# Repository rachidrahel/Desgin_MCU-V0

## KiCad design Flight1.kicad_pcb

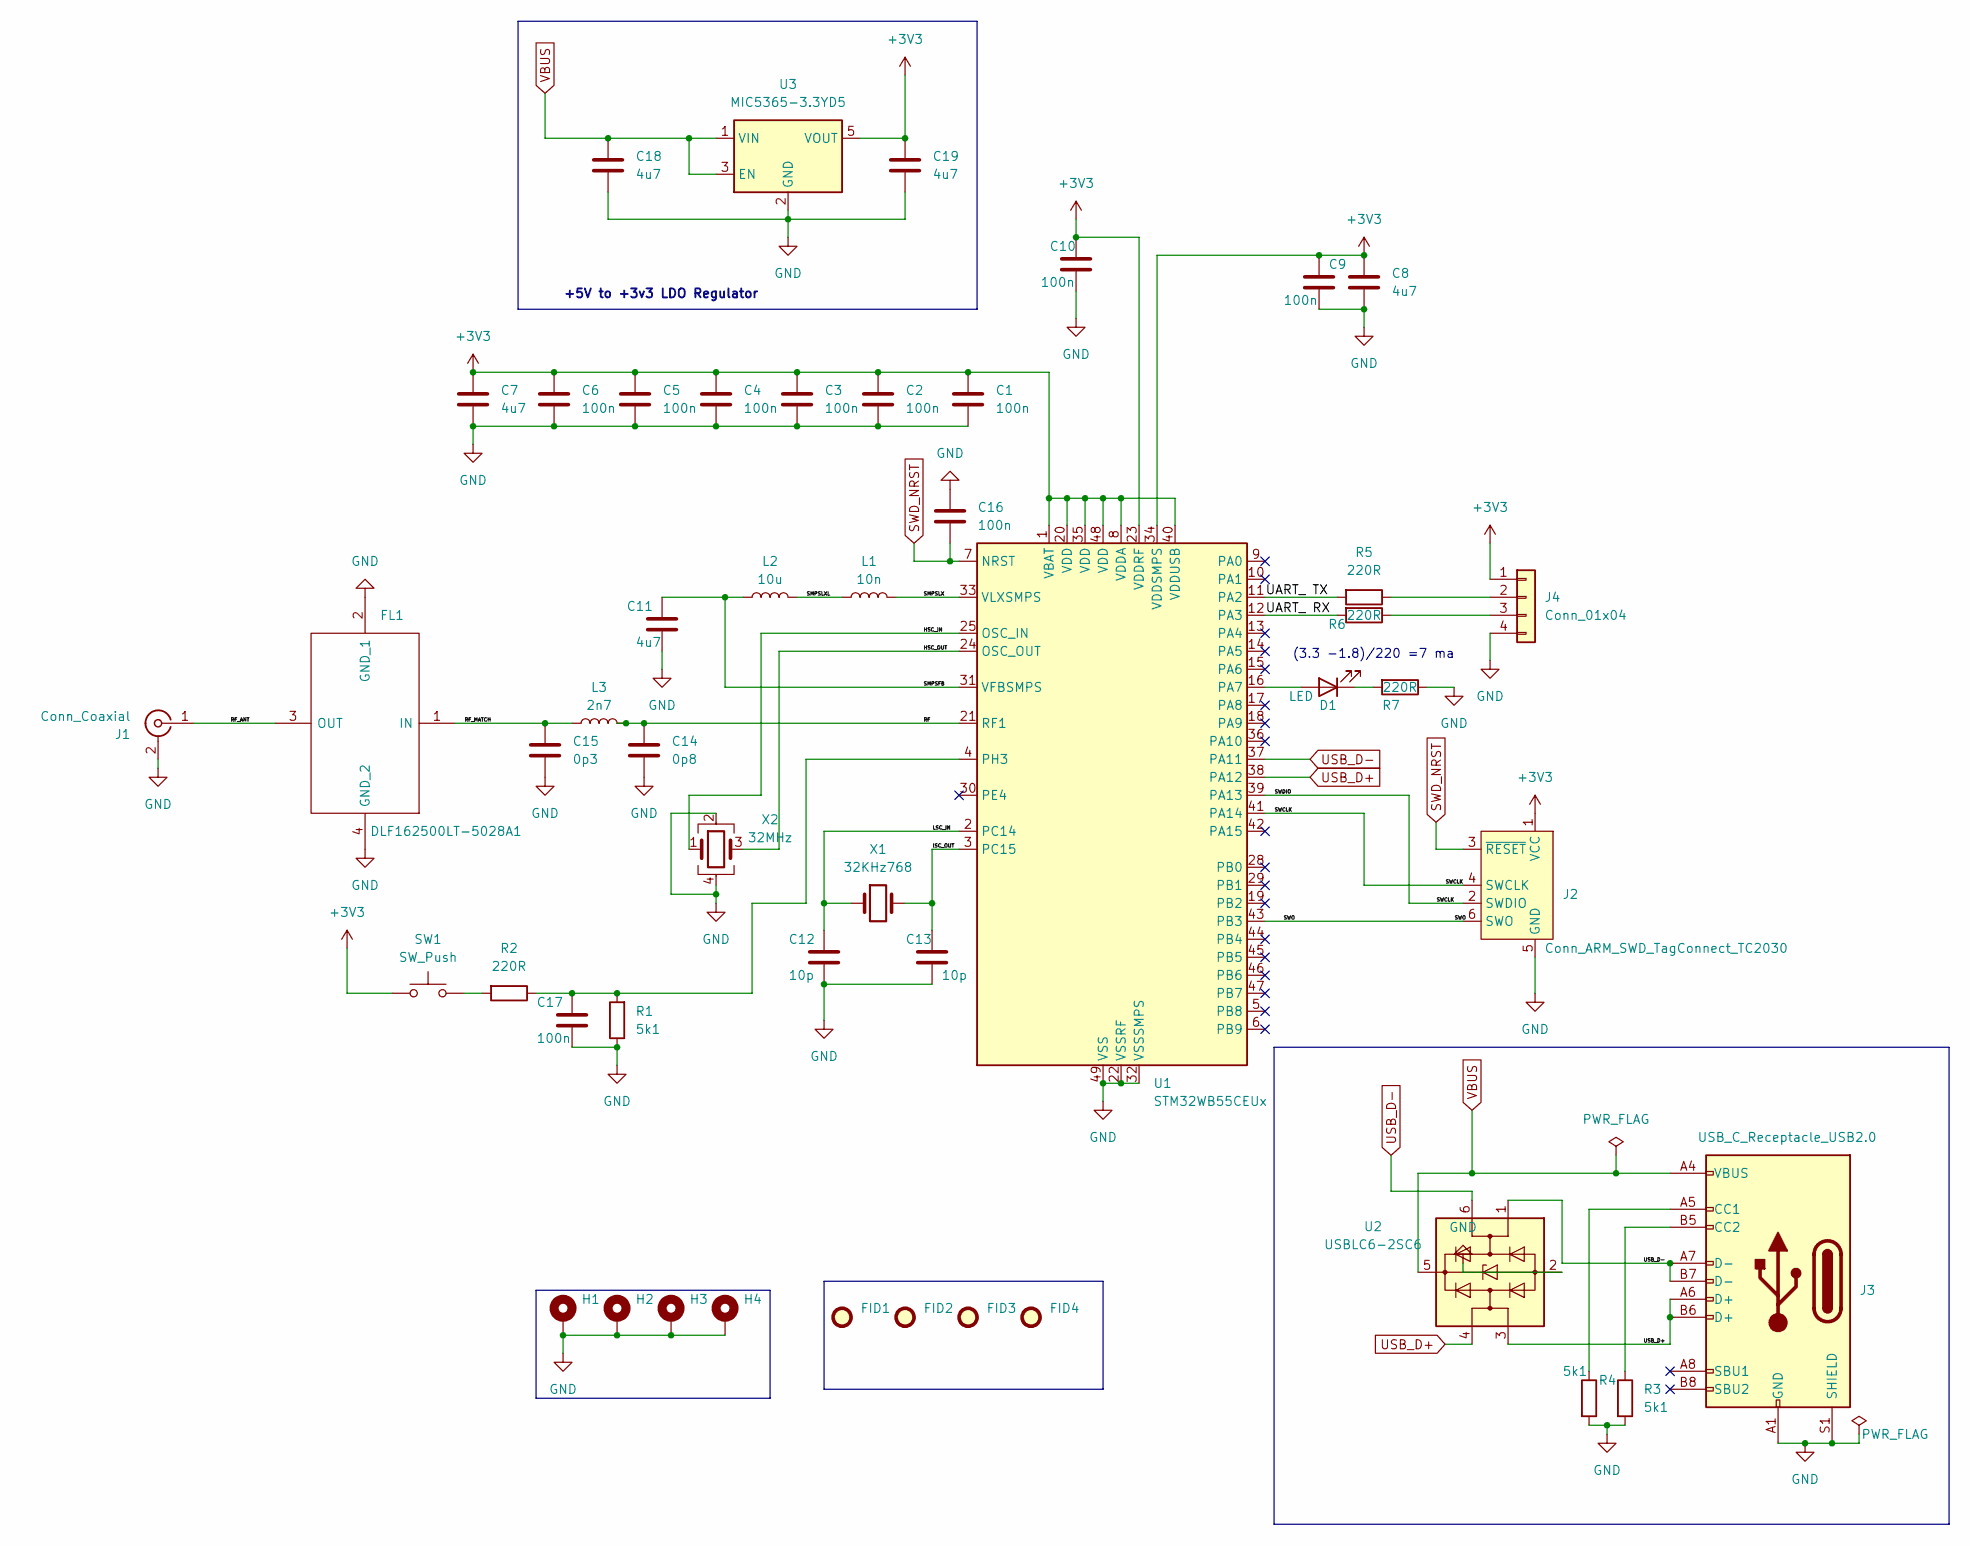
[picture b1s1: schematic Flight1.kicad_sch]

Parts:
C1, C2, C3, C4, C5, C6, C9, C10, C16, C17: 100n; C_0402_1005Metric
C7, C8, C11, C18, C19: 4u7; C_0402_1005Metric
C12, C13: 10p; C_0402_1005Metric
C14: 0p8; C_0402_1005Metric
C15: 0p3; C_0402_1005Metric
D1: LED; LED_0402_1005Metric
FID1, FID2, FID3, FID4: Fiducial; Fiducial_0.5mm_Mask1.5mm
FL1: DLF162500LT-5028A1; DLF162500LT5028A1; Mouser Part Number 810-DLF16250LT5028A1
H1, H2, H3, H4: MountingHole_Pad; MountingHole_2.2mm_M2
J1: Conn_Coaxial; U.FL_Molex_MCRF_73412-0110_Vertical
J2: Conn_ARM_SWD_TagConnect_TC2030; Tag-Connect_TC2030-IDC-FP_2x03_P1.27mm_Vertical
J3: USB_C_Receptacle_USB2.0; USB_C_Receptacle_GCT_USB4105-xx-A_16P_TopMnt_Horizontal
J4: Conn_01x04; Molex_PicoBlade_53048-0410_1x04_P1.25mm_Horizontal
L1: 10n; L_0402_1005Metric
L2: 10u; L_0805_2012Metric
L3: 2n7; L_0402_1005Metric
R1, R3, R4: 5k1; R_0402_1005Metric
R2, R5, R6, R7: 220R; R_0402_1005Metric
SW1: SW_Push; SW_SPST_CK_RS282G05A3
U1: STM32WB55CEUx; QFN-48-1EP_7x7mm_P0.5mm_EP5.6x5.6mm
U2: USBLC6-2SC6; SOT-23-6
U3: MIC5365-3.3YD5; SOT-23-5
X1: 32KHz768; Crystal_SMD_2012-2Pin_2.0x1.2mm
X2: 32MHz; Crystal_SMD_2016-4Pin_2.0x1.6mm

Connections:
+3V3: C1.1, C2.1, C3.1, C4.1, C5.1, C6.1, C7.1, C8.1, C9.1, C10.1, C19.1, J2.1 (VCC), J4.1, SW1.1, U1.1 (VBAT), U1.8 (VDDA), U1.20 (VDD), U1.23 (VDDRF), U1.34 (VDDSMPS), U1.35 (VDD), U1.40 (VDDUSB), U1.48 (VDD), U3.5 (VOUT)
/HSC_IN: U1.25 (OSC_IN), X2.1
/HSC_OUT: U1.24 (OSC_OUT), X2.3
/LSC_IN: C12.1, U1.2 (PC14), X1.1
/RF: C14.1, L3.2, U1.21 (RF1)
/RF_ANT: FL1.3 (OUT), J1.1 (In)
/RF_MATCH: C15.1, FL1.1 (IN), L3.1
/SMPSFB: C11.1, L2.1, U1.31 (VFBSMPS)
/SMPSLX: L1.2, U1.33 (VLXSMPS)
/SMPSLXL: L1.1, L2.2
/SWCLK: J2.2 (SWDIO), J2.4 (SWCLK), U1.39 (PA13), U1.41 (PA14)
/SWO: J2.6 (SWO), U1.43 (PB3)
/UART_ RX: R6.2, U1.12 (PA3)
/UART_ TX: R5.2, U1.11 (PA2)
/lSC_OUT: C13.1, U1.3 (PC15), X1.2
GND: C1.2, C2.2, C3.2, C4.2, C5.2, C6.2, C7.2, C8.2, C9.2, C10.2, C11.2, C12.2, C13.2, C14.2, C15.2, C16.1, C17.2, C18.2, C19.2, FL1.2 (GND_1), FL1.4 (GND_2), H1.1, H2.1, H3.1, H4.1, J1.2 (Ext), J2.5 (GND), J3.A1 (GND), J3.A12 (GND), J3.B1 (GND), J3.B12 (GND), J3.S1 (SHIELD), J4.4, R1.1, R3.2, R4.2, R7.1, U1.22 (VSSRF), U1.32 (VSSSMPS), U1.49 (VSS), U2.2 (GND), U3.2 (GND), X2.2, X2.4
unnamed: D1.2 (A), U1.16 (PA7)
unnamed: D1.1 (K), R7.2
unnamed: J3.A5 (CC1), R4.1
unnamed: J3.B5 (CC2), R3.1
unnamed: J4.2, R5.1
unnamed: J4.3, R6.1
unnamed: R2.2, SW1.2
unnamed: C17.1, R1.2, R2.1, U1.4 (PH3)
SWD_NRST: C16.2, J2.3 (~RESET), U1.7 (NRST)
USB_D+: J3.A6 (D+), J3.B6 (D+), U1.38 (PA12), U2.3 (I/O2), U2.4 (I/O2)
USB_D-: J3.A7 (D-), J3.B7 (D-), U1.37 (PA11), U2.1 (I/O1), U2.6 (I/O1)
VBUS: C18.1, J3.A4 (VBUS), J3.A9 (VBUS), J3.B4 (VBUS), J3.B9 (VBUS), U2.5 (VBUS), U3.1 (VIN), U3.3 (EN)

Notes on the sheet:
+5V to +3v3 LDO Regulator
(3.3 -1.8)/220 =7 ma

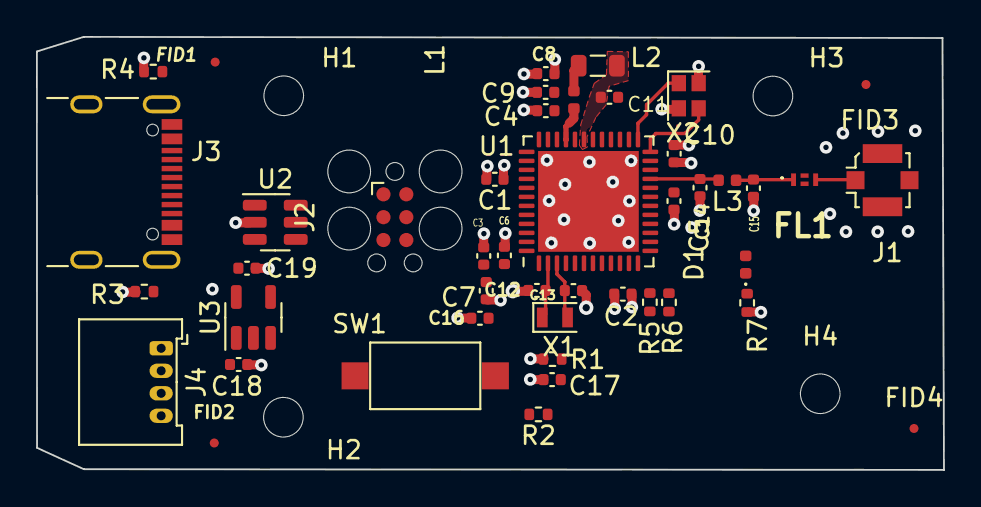
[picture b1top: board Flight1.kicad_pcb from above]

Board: 4 copper layers, 50.4 x 24.1 mm, 49 parts (0 on the bottom side), 28 nets.
